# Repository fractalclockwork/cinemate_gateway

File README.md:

# cinemate-gateway

A Raspberry Pi Pico receives the Bose CineMate universal remote in AUX mode and types ordinary USB HID keystrokes and mouse motion into Chrome on Linux.

Phase 1 does not transmit IR toward the CineMate Interface. The only IR LED on the bench is for a short optical loopback.

License: [MIT](LICENSE).

## Host check

These run with no Pico attached and no operator flags set:

```bash
python3 -m venv .venv
.venv/bin/pip install -r requirements.txt
make check
make sim
```

`make check` runs the decode, keymap, and HID report tests. `make sim` prints one synthetic HID fixture.

## On the bench

The operator sets the flags; agents must not.

```bash
export OPERATOR_VERIFY=1
make stage BOARD=pico STAGE=present
make stage BOARD=pico STAGE=workflow

export OPERATOR_VERIFY=1 OPERATOR_FLASH=1
make firmware
```

Button codes are learned by listening to the remote and then mapping what was heard. That is a capture session, not a lesson:

```bash
OPERATOR_VERIFY=1 make capture FRESH=1
```

Bring-up detail is in [`hardware/docs/bringup.md`](hardware/docs/bringup.md), pins and CircuitPython in [`hardware/docs/boards/pico.md`](hardware/docs/boards/pico.md), and the dev-host image in [`environment/README.md`](environment/README.md).

## Amazon keymap

The active map is [`software/keymap.yaml`](software/keymap.yaml) (profile amazon, AUX Sony DVR `20636`). Regenerate the on-device fragment with `make firmware-keymap`. Player shortcuts and focus notes are in [`docs/remote/amazon-chrome-shortcuts.md`](docs/remote/amazon-chrome-shortcuts.md).

## Docs

| Doc | What it is |
| --- | --- |
| [`docs/SPEC.md`](docs/SPEC.md) | Product requirements |
| [`STATUS.md`](STATUS.md) | What is decided and what is still open |
| [`docs/methodology/operator-loop.md`](docs/methodology/operator-loop.md) | What the host may prove, and what the operator confirms |
| [`docs/design-process.md`](docs/design-process.md) | How this repo was designed, including the board and bring-up |
| [`docs/kicad/ir-gateway/`](docs/kicad/ir-gateway/) | Wire-wrap protoboard |

## Later

A small web app may eventually drive IR transmit for CineMate power and volume alongside the same browser keys. That work needs a new operator flag before any IR is aimed at the Interface. See [`docs/SPEC.md`](docs/SPEC.md).

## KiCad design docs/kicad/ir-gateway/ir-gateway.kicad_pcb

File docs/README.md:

# Documentation index

| Area | Paths |
| --- | --- |
| Spec / status | [`SPEC.md`](SPEC.md) (requirements), [`../STATUS.md`](../STATUS.md) (session handoff), [`manual-facts.md`](manual-facts.md) |
| Bring-up / remote | [`../hardware/docs/bringup.md`](../hardware/docs/bringup.md), [`remote/`](remote/) (inventory, blink worksheet, player matrix, [`amazon-chrome-shortcuts.md`](remote/amazon-chrome-shortcuts.md), [`youtubetv-chrome-shortcuts.md`](remote/youtubetv-chrome-shortcuts.md)), [`chrome-troubleshooting.md`](chrome-troubleshooting.md) |
| Method | [`design-process.md`](design-process.md) (article), [`methodology/operator-loop.md`](methodology/operator-loop.md), [`../AGENTS.md`](../AGENTS.md) |
| Design / decisions | [`kicad/ir-gateway/`](kicad/ir-gateway/), [`decisions/`](decisions/) |
| History / publish | [`history/postmortem-agentic-bringup.md`](history/postmortem-agentic-bringup.md) (archived bring-up), [`github-readiness.md`](github-readiness.md) |

Product manuals are not in this tree. Treat any copy kept beside the repo as a third-party reference, not an inventable IR dump.

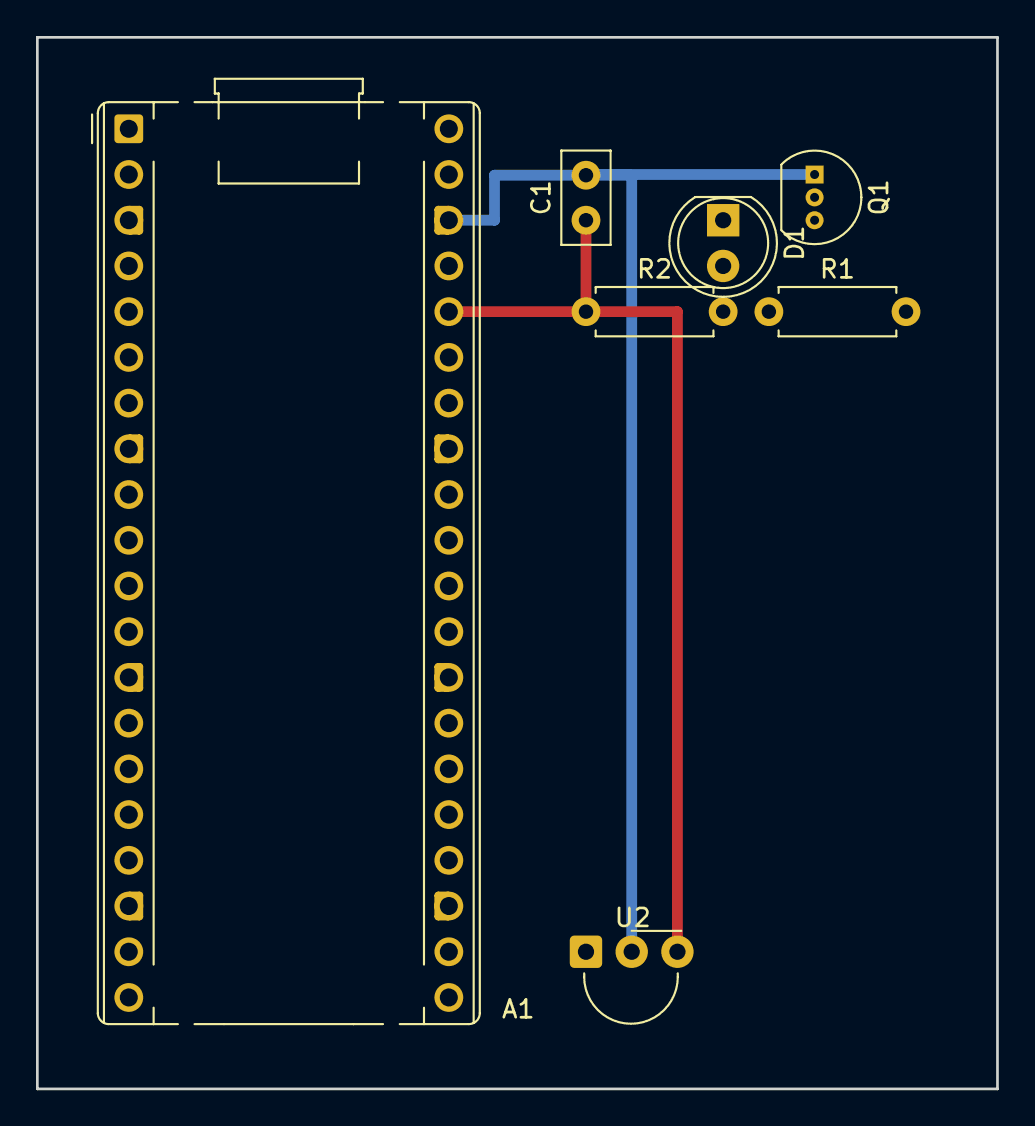
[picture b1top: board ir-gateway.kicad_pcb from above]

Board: 14 copper layers, 53.3 x 58.4 mm, 7 parts (0 on the bottom side), 7 nets.

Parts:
A1: RaspberryPi_Pico; RaspberryPi_Pico_Common_THT
C1: 100n; C_Disc_D5.0mm_W2.5mm_P2.50mm
D1: IR_LED; LED_D5.0mm
Q1: 2N3904; TO-92_Inline
R1: 1k; R_Axial_DIN0207_L6.3mm_D2.5mm_P7.62mm_Horizontal
R2: 100; R_Axial_DIN0207_L6.3mm_D2.5mm_P7.62mm_Horizontal
U2: CHQ1838; Vishay_MINIMOLD-3Pin

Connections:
+3V3: A1.36, C1.1, R2.1, U2.3
GND: A1.38, C1.2, Q1.1, U2.2
IR_RX: A1.19, U2.1
IR_TX: A1.20, R1.1
LED_A: D1.2, R2.2
LED_K: D1.1, Q1.3
Q1_B: Q1.2, R1.2
